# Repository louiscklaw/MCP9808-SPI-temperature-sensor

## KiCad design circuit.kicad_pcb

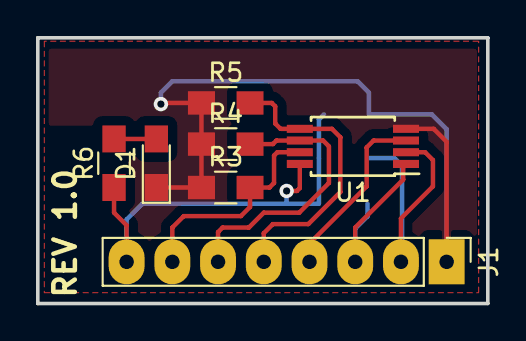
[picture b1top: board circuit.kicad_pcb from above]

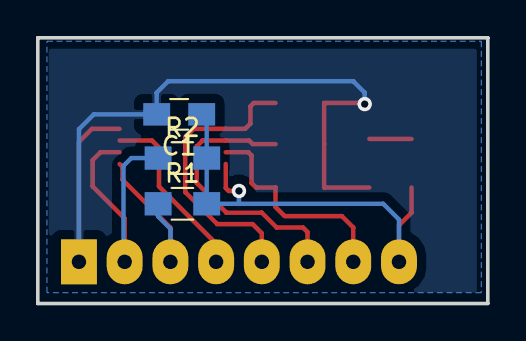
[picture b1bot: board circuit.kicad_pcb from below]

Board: 2 copper layers, 25.0 x 14.8 mm, 10 parts (3 on the bottom side), 9 nets.

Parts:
C1: 105; C_0805_HandSoldering
D1: LED; LED_0805_HandSoldering
J1: Conn_01x08; Pin_Header_Straight_1x08_Pitch2.54mm
R1, R2, R3, R4, R5: 103; R_0805_HandSoldering
R6: 1k; R_0805_HandSoldering
U1: MCP9808; TSSOP-8_4.4x3mm_Pitch0.65mm

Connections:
/A0: J1.7, R3.2, U1.7
/A1: J1.6, R4.2, U1.6
/A2: J1.5, R5.2, U1.5
/ALERT: J1.4, U1.3
/SCL: J1.2, R2.1, U1.2
/SDA: J1.3, R1.1, U1.1
GND: C1.2, D1.1, J1.1, R3.1, R4.1, R5.1, U1.4
unnamed: D1.2, R6.2
VDD: C1.1, J1.8, R1.2, R2.2, R6.1, U1.8

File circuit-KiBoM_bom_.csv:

Component,Description,Part,References,Value,Footprint,Quantity Per PCB,Datasheet,Field4
1,Unpolarized capacitor,C,C1,105,C_0805_HandSoldering,1,~,0805
2,LED generic,LED,D1,LED,LED_0805_HandSoldering,1,~,0805
3,"Generic connector, single row, 01x08, script generated (kicad-library-utils/schlib/autogen/connector/)",Conn_01x08,J1,Conn_01x08,Pin_Header_Straight_1x08_Pitch2.54mm,1,~,
4,Resistor,R,R6,102,R_0805_HandSoldering,1,~,0805
5,Resistor,R,R1 R2 R3 R4 R5,103,R_0805_HandSoldering,5,~,0805
6,,MCP9808,U1,MCP9808,TSSOP-8_4.4x3mm_Pitch0.65mm,1,,TSSOP-8





Component Groups:,6
Component Count:,10
Fitted Components:,10
Number of PCBs:,1
Total components:,10
Schematic Version:,
Schematic Date:,
BoM Date:,Sun Oct  7 01:20:00 2018
Schematic Source:,/home/logic/_workspace/kicad/MCP9808-SPI-temperature-sensor/circuit/circuit.sch
KiCad Version:,Eeschema 5.0.0-fee4fd1~66~ubuntu18.04.1

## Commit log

2018-10-06 init commit,
2018-11-18 update,
2020-05-06 ci: init travis build config,
2020-05-06 ci: init travis token,
